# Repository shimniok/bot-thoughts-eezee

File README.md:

A variety of gizmos I created to make breadboard prototyping quick and easy:

* [eeZeeAmp](https://github.com/shimniok/eeZeeAmp) - LM386 circuit, breakout
* [eeZee Tiny](https://github.com/shimniok/eeZeeTiny) - a breadboard target / breakout for 8-pin ATtiny chips
* [eeZee Medium Tiny](https://github.com/shimniok/eeZeeMedTiny) - a breadboard target / breakout for 14-pin ATtiny24/44/84
* [eeZee Tiny841](https://github.com/shimniok/eeZeeTiny841) - breakout for powerful new ATtiny841
* [eeZee Big Tiny](https://github.com/shimniok/eeZeeBigTiny) - a breadboard target / breakout for 20-pin ATtiny2313/4313
* [eeZee Prop](https://github.com/shimniok/eeZeeProp) - breadboard friendly, low cost Propeller board
* [eeZee LED](https://github.com/shimniok/eeZeeLED) - LED + resistor breakout for breadboard
* [eeZee microSD](https://github.com/shimniok/eeZeeMicroSD) - add an SD card to your breadboard Arduino / AVR
* [eeZee Pot](https://github.com/shimniok/eeZeePot)
* [eeZee Power](https://github.com/shimniok/eeZeePower) - small, simple, 5V/3.3V convenient USB breadboard power adapter
* [eeZee PowerJack](https://github.com/shimniok/eeZeePowerJack) - small, simple 5V breadboard power adapter with 2.1mm jack
* [eeZee RGB](https://github.com/shimniok/eeZeeRGB) - WS2812B smart RGB LED breakout
* [eeZee Switch](https://github.com/shimniok/eeZeeSwitch) - breadboard switch with debounce, pull-up
* [eeZee Crystal](https://github.com/shimniok/eeZeeCrystal) - clean up your Arduino / AVR breadboard
* [eeZee VGA](http://github.com/shimniok/eeZeeVGA) - VGA breadboard adapter for Propeller

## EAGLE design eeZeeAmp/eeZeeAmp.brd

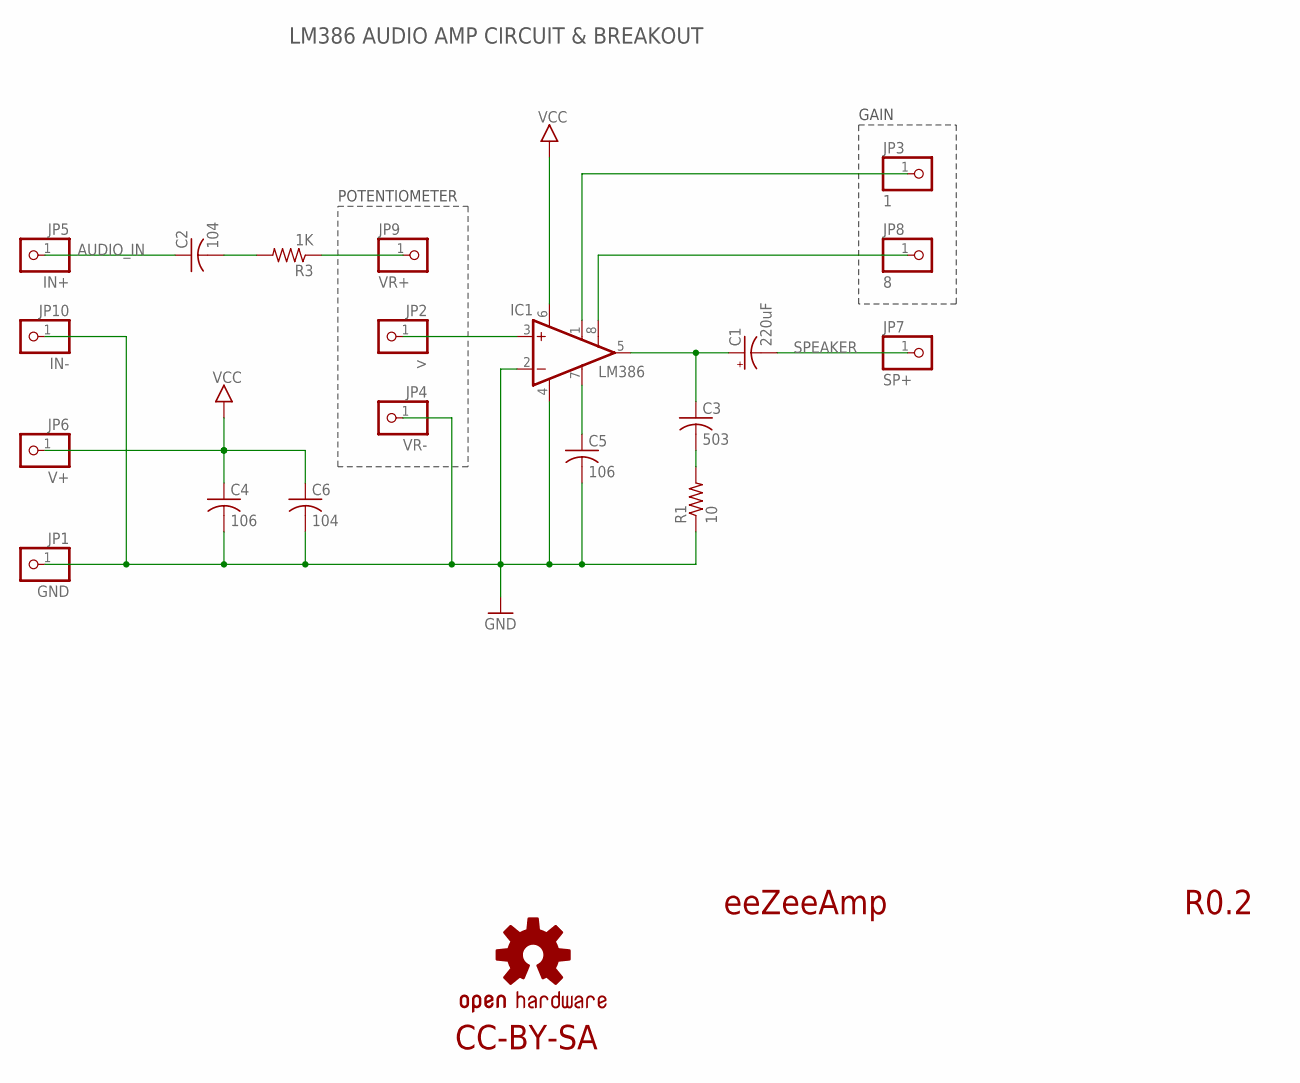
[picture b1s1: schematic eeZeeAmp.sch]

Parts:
C1: 220uF; E3,5-8
C2, C6: 104; C0603
C3: 503; C0603
C4, C5: 106; C1206
IC1: LM386; SO08
JP1: GND; 1X01-S
JP2: >; 1X01-S
JP3: 1; 1X01-S
JP4: VR-; 1X01-S
JP5: IN+; 1X01-S
JP6: V+; 1X01-S
JP7: SP+; 1X01-S
JP8: 8; 1X01-S
JP9: VR+; 1X01-S
JP10: IN-; 1X01-S
LOGO2: OSHW-LOGOS; OSHW-LOGO-S
R1: 10; R0603
R3: 1K; R0603

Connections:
1: IC1.1 (GAIN), JP3.1
3: IC1.3 (+IN), JP2.1
5: C1.+, C3.1, IC1.5 (OUT)
7: C5.1, IC1.7 (BYPASS)
8: IC1.8 (GAIN), JP8.1
AUDIO_IN: C2.1, JP5.1
GND: C4.2, C5.2, C6.2, IC1.2 (-IN), IC1.4 (GND), JP1.1, JP4.1, JP10.1, R1.1
unnamed: C2.2, R3.2
unnamed: C3.2, R1.2
unnamed: JP9.1, R3.1
SPEAKER: C1.-, JP7.1
VCC: C4.1, C6.1, IC1.6 (VS), JP6.1

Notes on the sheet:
eeZeeAmp
R0.2
POTENTIOMETER
LM386 AUDIO AMP CIRCUIT & BREAKOUT
GAIN
CC-BY-SA

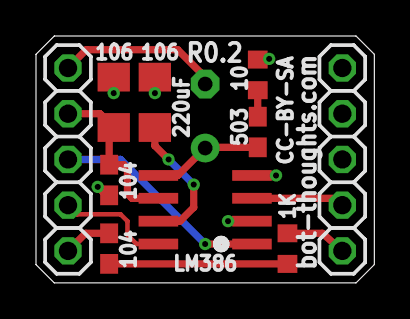
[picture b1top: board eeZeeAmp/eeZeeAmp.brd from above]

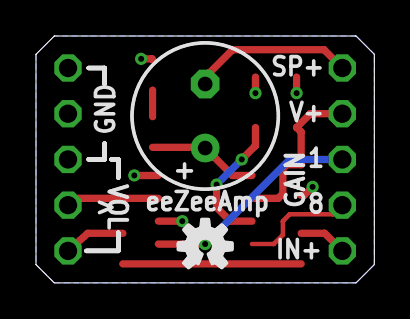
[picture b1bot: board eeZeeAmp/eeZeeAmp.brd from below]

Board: 2 copper layers, 18.8 x 13.7 mm, 20 parts (2 on the bottom side), 12 nets.

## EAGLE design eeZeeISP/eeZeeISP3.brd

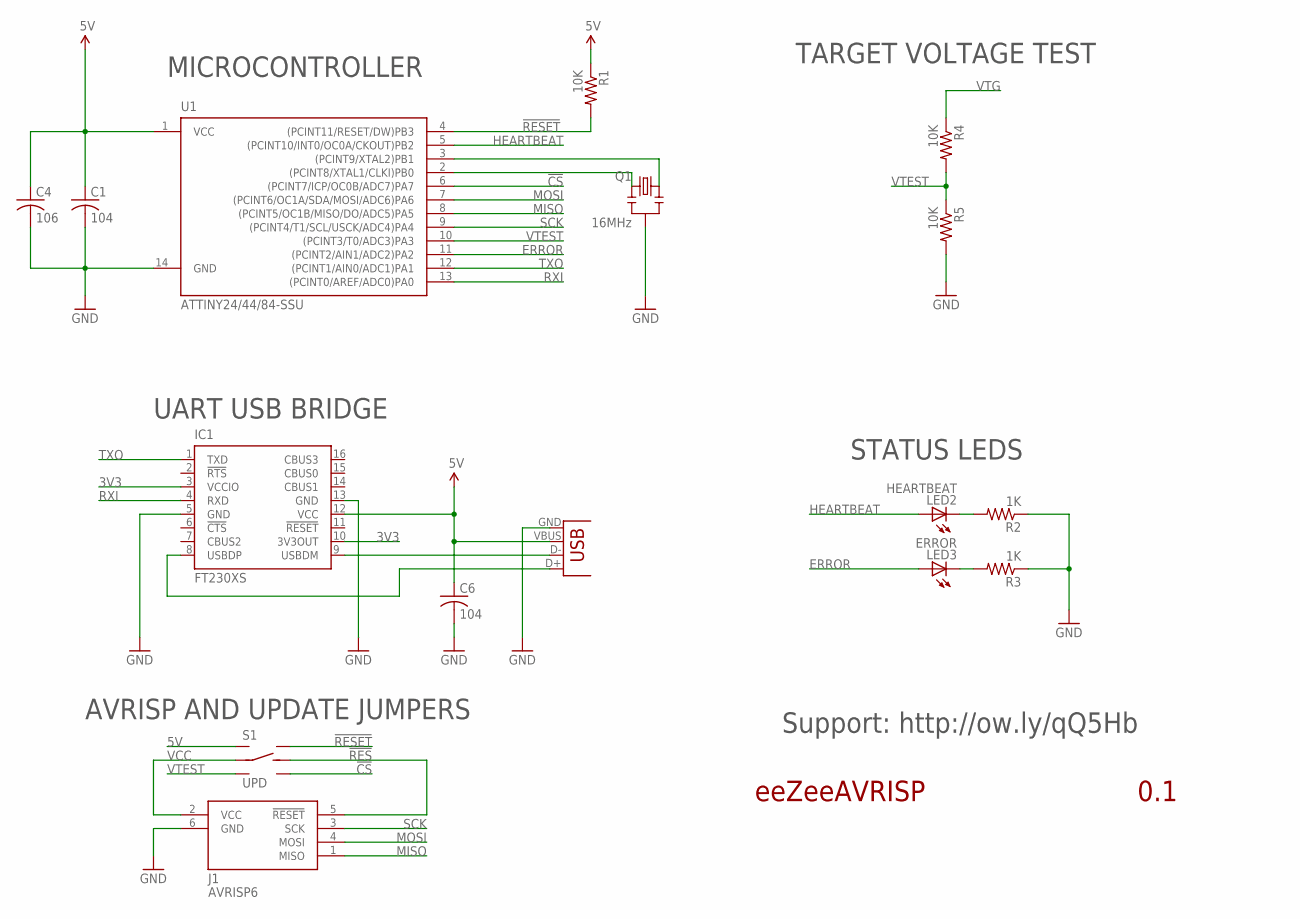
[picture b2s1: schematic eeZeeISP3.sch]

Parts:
C1, C6: 104; C0603
C4: 106; C0603
IC1: FT230XS; SSOP16
J1: AVRISP6; CON6P2R
LED2: HEARTBEAT; CHIPLED_1206
LED3: ERROR; CHIPLED_1206
Q1: 16MHz; CSTCE_V_C
R1, R4, R5: 10K; R0603
R2, R3: 1K; R0603
S1: UPD; DPDT_JS202011CQN
U1: ATTINY24/44/84-SSU; SOIC14
X2: USB-SMD-NS; USB-MINIB-NOSTOP

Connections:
3V3: IC1.3 (VCCIO), IC1.10 (3V3OUT)
5V: C1.1, C4.1, C6.1, IC1.12 (VCC), R1.1, S1.1 (L1), U1.1 (VCC), X2.VBUS
!CS: S1.6 (R2), U1.6 ((PCINT7/ICP/OC0B/ADC7)PA7)
!RES: J1.5 (!RESET), S1.5 (RC)
!RESET: R1.2, S1.4 (R1), U1.4 ((PCINT11/RESET/DW)PB3)
ERROR: LED3.A, U1.11 ((PCINT2/AIN1/ADC2)PA2)
GND: C1.2, C4.2, C6.2, IC1.5 (GND), IC1.13 (GND), J1.6 (GND), Q1.GND, R2.1, R3.1, R5.2, U1.14 (GND), X2.GND
HEARTBEAT: LED2.A, U1.5 ((PCINT10/INT0/OC0A/CKOUT)PB2)
MISO: J1.1 (MISO), U1.8 ((PCINT5/OC1B/MISO/DO/ADC5)PA5)
MOSI: J1.4 (MOSI), U1.7 ((PCINT6/OC1A/SDA/MOSI/ADC6)PA6)
unnamed: Q1.X1, U1.3 ((PCINT9/XTAL2)PB1)
unnamed: IC1.8 (USBDP), X2.D+
unnamed: LED2.C, R2.2
unnamed: LED3.C, R3.2
unnamed: Q1.X2, U1.2 ((PCINT8/XTAL1/CLKI)PB0)
unnamed: IC1.9 (USBDM), X2.D-
RXI: IC1.4 (RXD), U1.13 ((PCINT0/AREF/ADC0)PA0)
SCK: J1.3 (SCK), U1.9 ((PCINT4/T1/SCL/USCK/ADC4)PA4)
TXO: IC1.1 (TXD), U1.12 ((PCINT1/AIN0/ADC1)PA1)
VCC: J1.2 (VCC), S1.2 (LC)
VTEST: R4.2, R5.1, S1.3 (L2), U1.10 ((PCINT3/T0/ADC3)PA3)
VTG: R4.1

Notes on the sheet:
eeZeeAVRISP
0.1
AVRISP AND UPDATE JUMPERS
TARGET VOLTAGE TEST
STATUS LEDS
UART USB BRIDGE
MICROCONTROLLER
Support: http://ow.ly/qQ5Hb

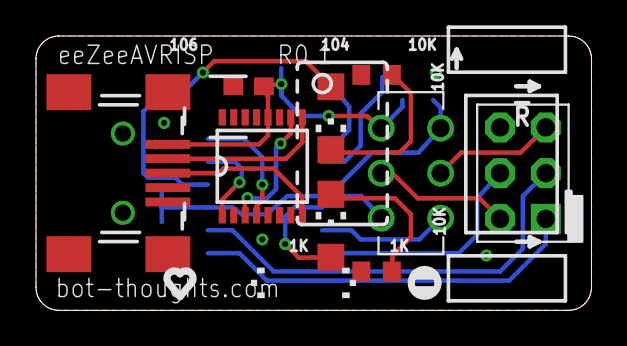
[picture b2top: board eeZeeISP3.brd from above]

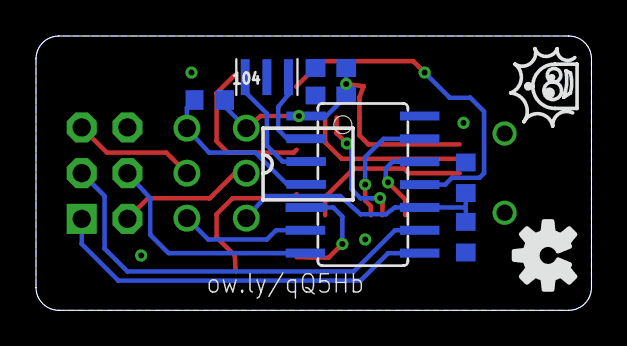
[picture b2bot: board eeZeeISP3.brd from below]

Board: 2 copper layers, 30.9 x 15.2 mm, 16 parts (7 on the bottom side), 21 nets.

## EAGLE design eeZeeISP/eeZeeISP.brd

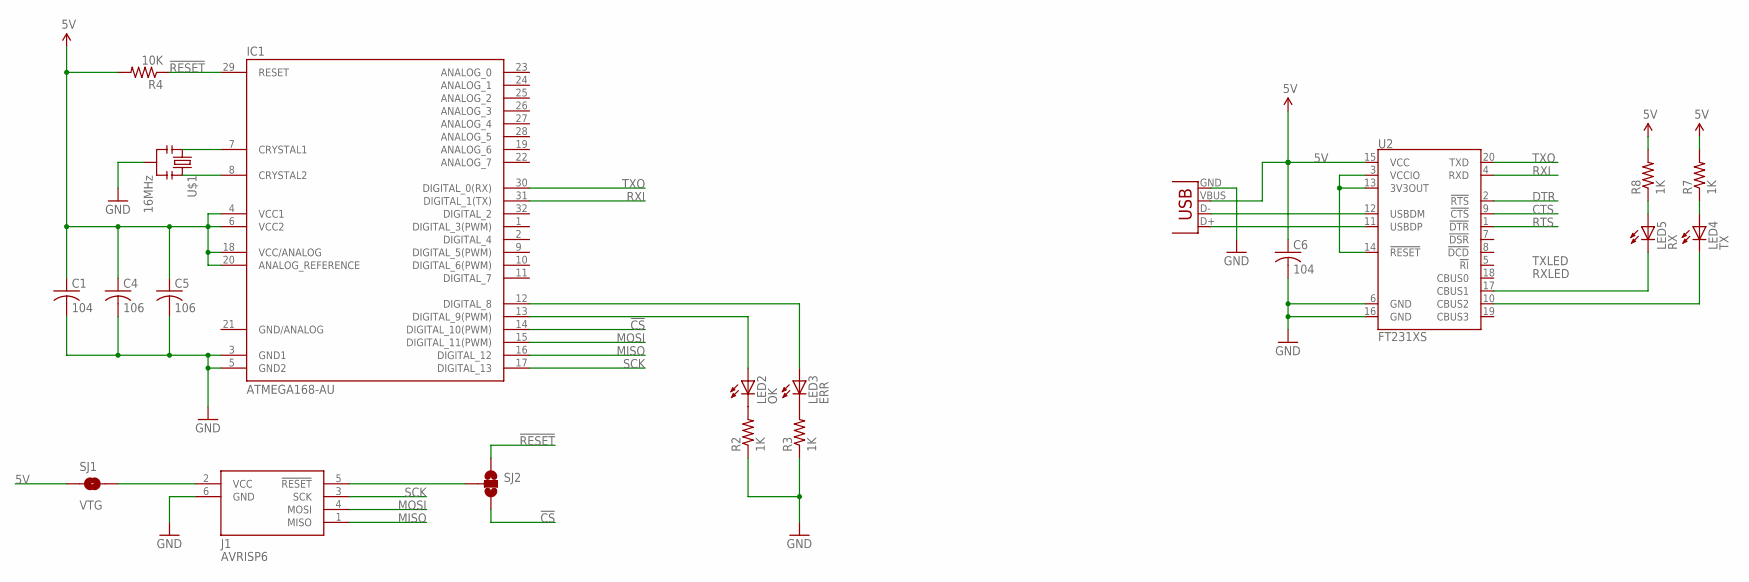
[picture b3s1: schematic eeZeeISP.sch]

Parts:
C1, C6: 104; C0603
C4, C5: 106; C0603
IC1: ATMEGA168-AU; TQFP32-08
J1: AVRISP6; CON6P2R
LED2: OK; CHIPLED_1206
LED3: ERR; CHIPLED_1206
LED4: TX; CHIPLED_1206
LED5: RX; CHIPLED_1206
R2, R3, R7, R8: 1K; R0603
R4: 10K; R0603
SJ1: VTG; SJ_2S-NO
SJ2: SOLDERJUMPER_2WAYS; SJ_3
U2: FT231XS; SSOP20_L
U$1: 16MHz; CSTCE_V_C
X2: USB-SMD-NS; USB-MINIB-NOSTOP

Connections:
5V: C1.1, C4.1, C5.1, C6.1, IC1.4 (VCC1), IC1.6 (VCC2), IC1.18 (VCC/ANALOG), IC1.20 (ANALOG_REFERENCE), R4.2, R7.2, R8.2, SJ1.1, U2.15 (VCC), X2.VBUS
!CS: IC1.14 (DIGITAL_10(PWM)), SJ2.3
!RESET: IC1.29 (RESET), R4.1, SJ2.1
CTS: U2.9 (!CTS)
DTR: U2.1 (!DTR)
GND: C1.2, C4.2, C5.2, C6.2, IC1.3 (GND1), IC1.5 (GND2), J1.6 (GND), R2.1, R3.1, U2.6 (GND), U2.16 (GND), U$1.GND, X2.GND
GND/ANALOG: IC1.21 (GND/ANALOG)
MISO: IC1.16 (DIGITAL_12), J1.1 (MISO)
MOSI: IC1.15 (DIGITAL_11(PWM)), J1.4 (MOSI)
unnamed: LED4.A, R7.1
unnamed: LED5.A, R8.1
unnamed: J1.2 (VCC), SJ1.2
unnamed: J1.5 (!RESET), SJ2.2
unnamed: IC1.13 (DIGITAL_9(PWM)), LED2.A
unnamed: IC1.12 (DIGITAL_8), LED3.A
unnamed: IC1.7 (CRYSTAL1), U$1.X1
unnamed: U2.3 (VCCIO), U2.13 (3V3OUT), U2.14 (!RESET)
unnamed: LED2.C, R2.2
unnamed: LED3.C, R3.2
unnamed: IC1.8 (CRYSTAL2), U$1.X2
RTS: U2.2 (!RTS)
RXI: IC1.31 (DIGITAL_1(TX)), U2.4 (RXD)
RXLED: LED5.C, U2.17 (CBUS1)
SCK: IC1.17 (DIGITAL_13), J1.3 (SCK)
TXLED: LED4.C, U2.10 (CBUS2)
TXO: IC1.30 (DIGITAL_0(RX)), U2.20 (TXD)
USB_D+: U2.11 (USBDP), X2.D+
USB_D-: U2.12 (USBDM), X2.D-

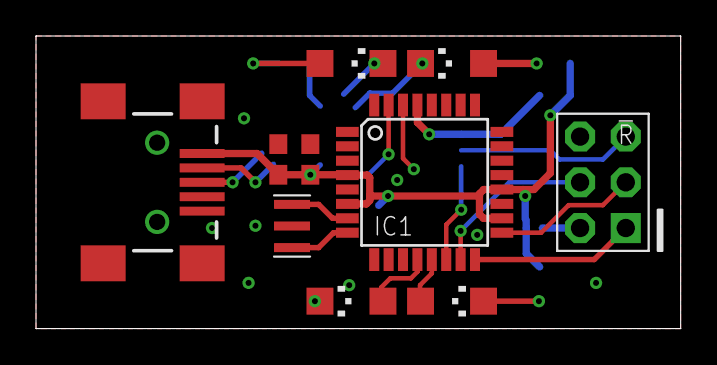
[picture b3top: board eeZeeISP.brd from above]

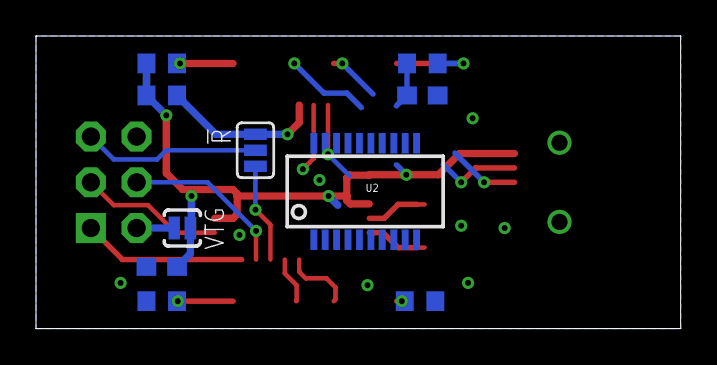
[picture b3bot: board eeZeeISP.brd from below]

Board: 2 copper layers, 35.8 x 16.3 mm, 20 parts (10 on the bottom side), 24 nets.

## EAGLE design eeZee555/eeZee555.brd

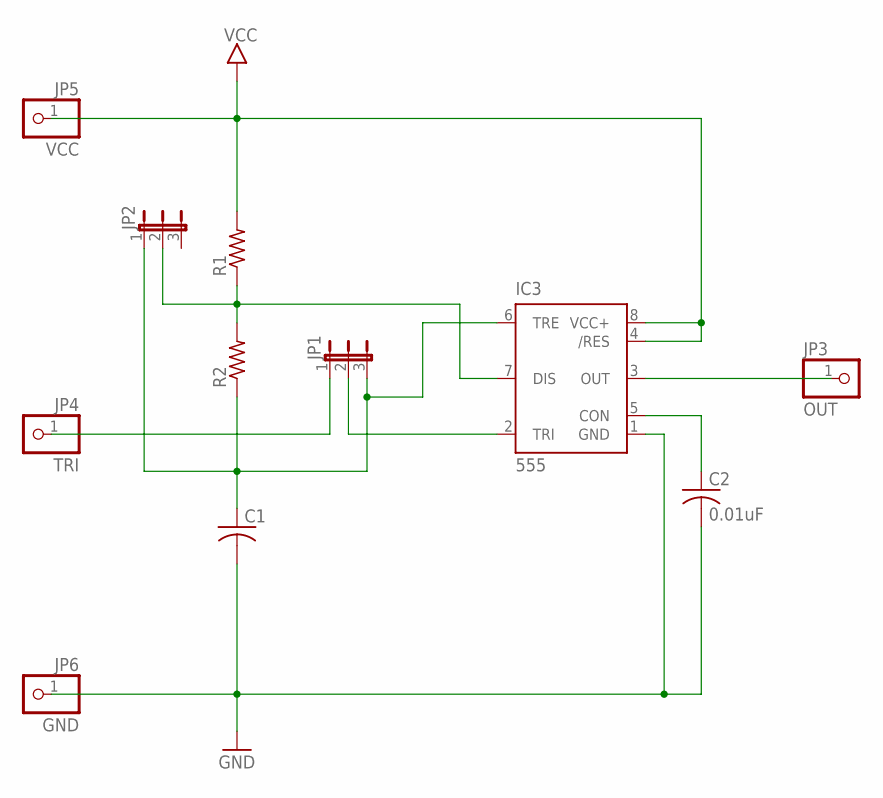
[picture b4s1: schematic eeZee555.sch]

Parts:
C1: C-US050-025X075; C050-025X075
C2: 0.01uF; C0603
IC3: 555; DIL-08
JP1, JP2: JP2E; JP2
JP3: OUT; 1X01-S
JP4: TRI; 1X01-S
JP5: VCC; 1X01-S
JP6: GND; 1X01-S
R1, R2: R-US_0204/5; 0204/5

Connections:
GND: C1.2, C2.2, IC3.1 (GND), JP6.1
unnamed: IC3.7 (DIS), JP2.2, R1.1, R2.2
unnamed: C1.1, IC3.6 (TRE), JP1.3, JP2.1, R2.1
unnamed: JP1.1, JP4.1
unnamed: IC3.2 (TRI), JP1.2
unnamed: IC3.3 (OUT), JP3.1
unnamed: C2.1, IC3.5 (CON)
VCC: IC3.4 (/RES), IC3.8 (VCC+), JP5.1, R1.2

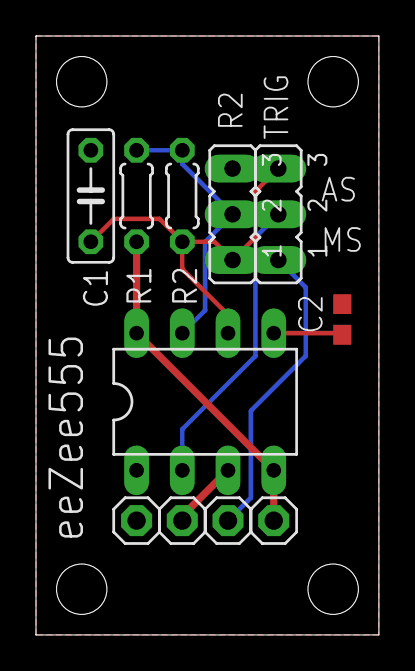
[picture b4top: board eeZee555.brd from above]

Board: 2 copper layers, 19.1 x 33.3 mm, 11 parts (0 on the bottom side), 8 nets.

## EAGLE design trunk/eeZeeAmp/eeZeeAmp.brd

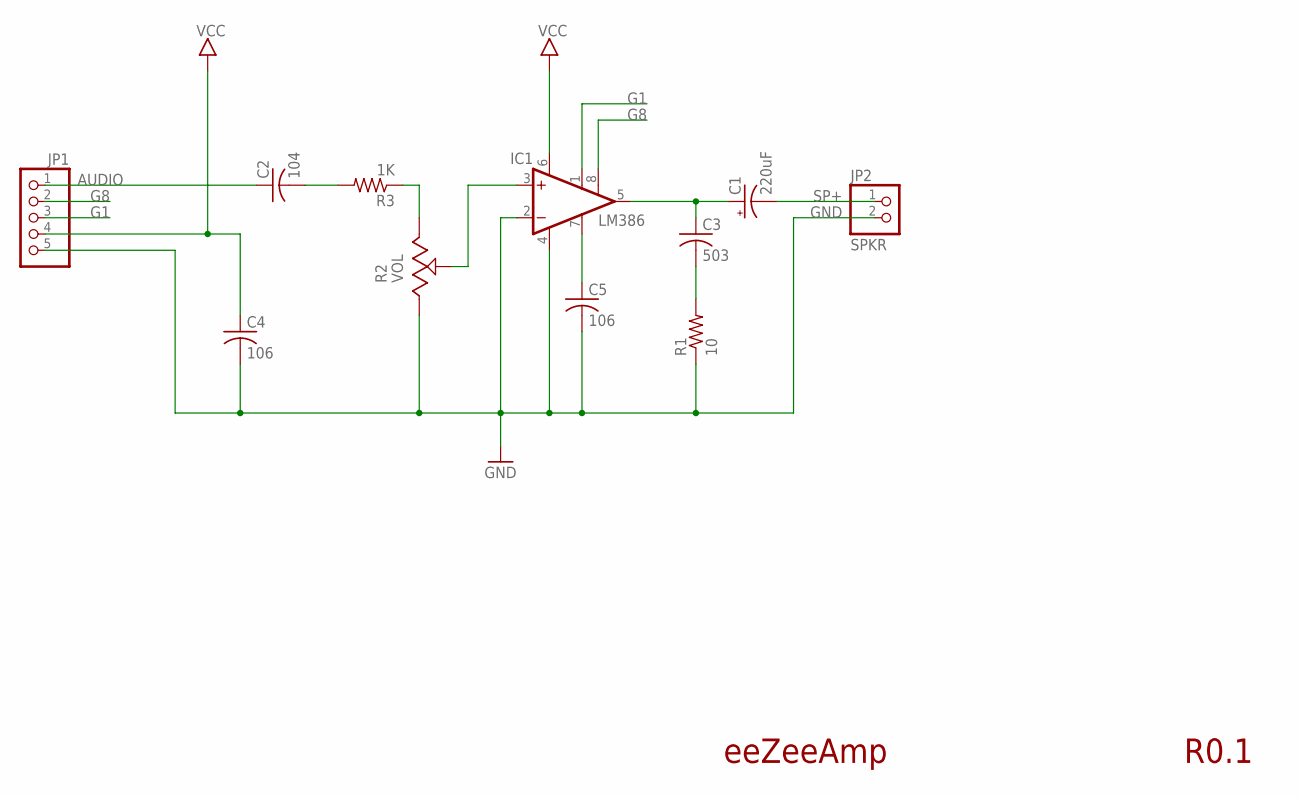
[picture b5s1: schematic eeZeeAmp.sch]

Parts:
C1: 220uF; E2,5-6
C2: 104; C0603
C3: 503; C0603
C4, C5: 106; C1206
IC1: LM386; SO08
JP1: PINHD-1X05_2.54-S; 1X05-S
JP2: SPKR; 1X02-S
R1: 10; R0603
R2: VOL; OFFBOARD_POT_3
R3: 1K; R0603

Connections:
AUDIO: C2.1, JP1.1
G1: IC1.1 (GAIN), JP1.3
G8: IC1.8 (GAIN), JP1.2
GND: C4.2, C5.2, IC1.2 (-IN), IC1.4 (GND), JP1.5, JP2.2, R1.1, R2.P$1 (A)
unnamed: IC1.3 (+IN), R2.P$2 (S)
unnamed: C2.2, R3.2
unnamed: C1.+, C3.1, IC1.5 (OUT)
unnamed: C3.2, R1.2
unnamed: C5.1, IC1.7 (BYPASS)
unnamed: R2.P$3 (E), R3.1
SP+: C1.-, JP2.1
VCC: C4.1, IC1.6 (VS), JP1.4

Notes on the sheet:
eeZeeAmp
R0.1

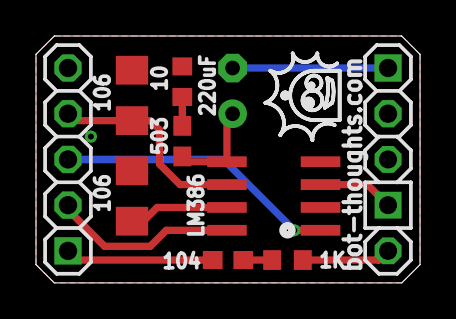
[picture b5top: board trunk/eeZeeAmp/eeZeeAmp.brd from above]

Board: 2 copper layers, 21.3 x 13.7 mm, 11 parts (1 on the bottom side), 12 nets.

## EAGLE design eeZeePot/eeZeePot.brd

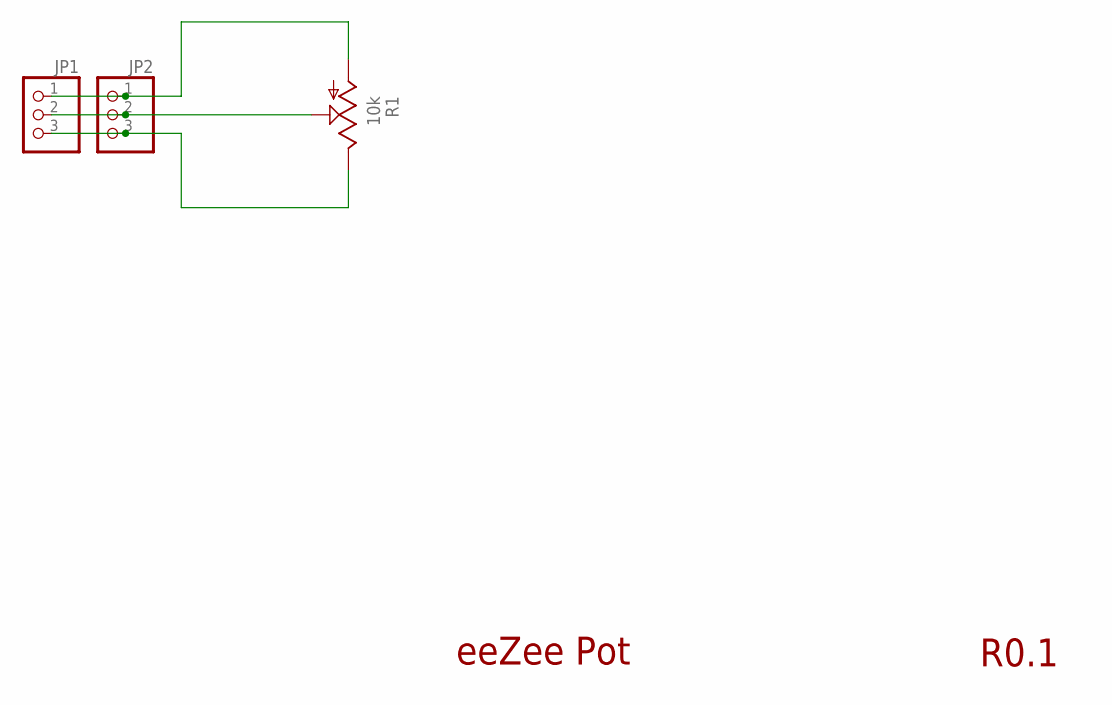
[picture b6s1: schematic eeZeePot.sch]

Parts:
JP1, JP2: PINHD-1X03_2.54-S; 1X03-S
R1: 10k; CA6V

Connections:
unnamed: JP1.1, JP2.1, R1.A
unnamed: JP1.2, JP2.2, R1.S
unnamed: JP1.3, JP2.3, R1.E

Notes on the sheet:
eeZee Pot
R0.1

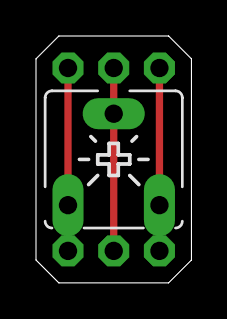
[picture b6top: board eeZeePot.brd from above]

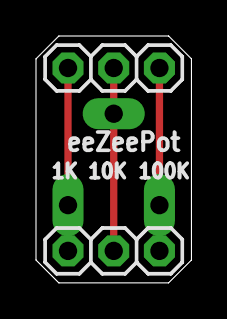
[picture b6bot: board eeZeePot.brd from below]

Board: 2 copper layers, 8.6 x 13.7 mm, 3 parts (2 on the bottom side), 3 nets.

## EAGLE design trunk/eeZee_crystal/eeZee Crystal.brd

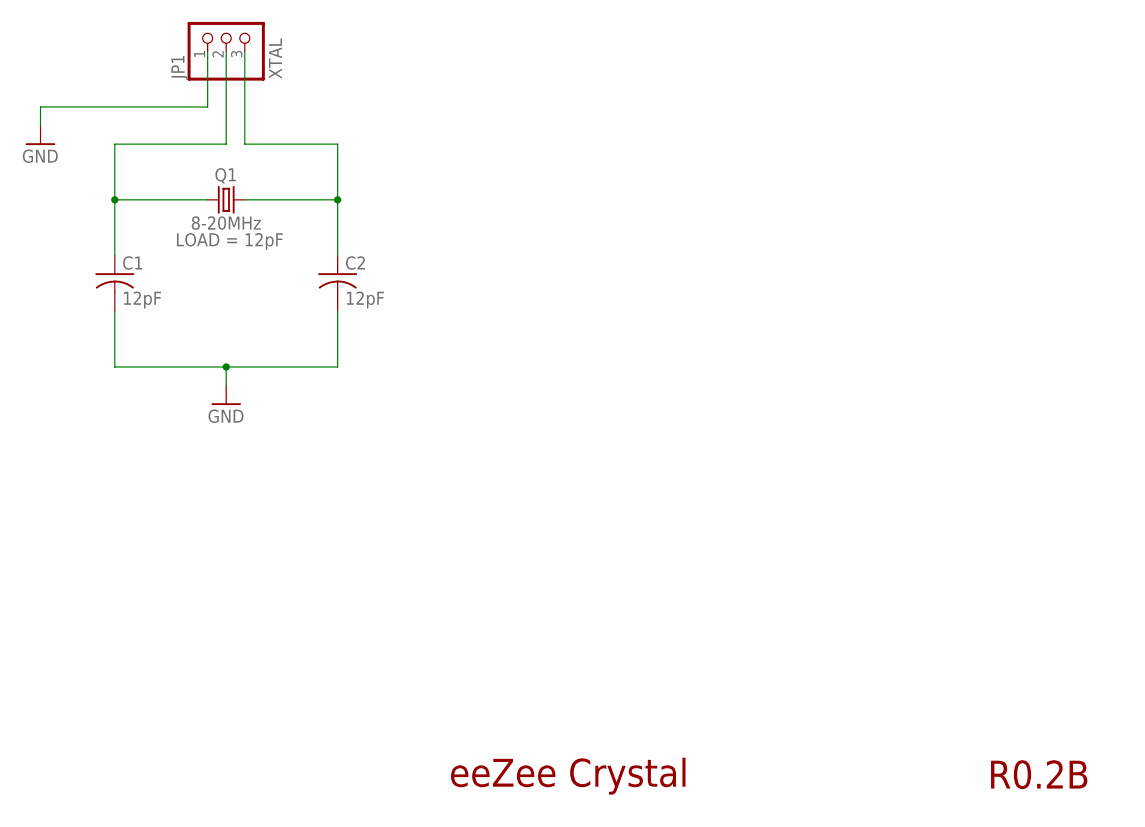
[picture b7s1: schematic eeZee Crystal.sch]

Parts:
C1, C2: 12pF; C0603; PARTNO C1608C0G1H080D
JP1: XTAL; 1X03-S
Q1: 8-20MHz; NDK_2PAD_5X3; PARTNO NX5032GA-16.000000MHZ-LN-CD-1

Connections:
GND: C1.2, C2.2, JP1.1
unnamed: C1.1, JP1.2, Q1.P$2 (2)
unnamed: C2.1, JP1.3, Q1.P$1 (1)

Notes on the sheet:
eeZee Crystal
R0.2B

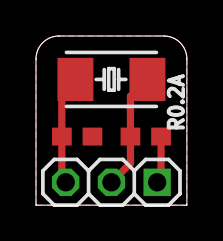
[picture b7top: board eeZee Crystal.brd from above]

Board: 2 copper layers, 8.4 x 9.4 mm, 4 parts (0 on the bottom side), 3 nets.

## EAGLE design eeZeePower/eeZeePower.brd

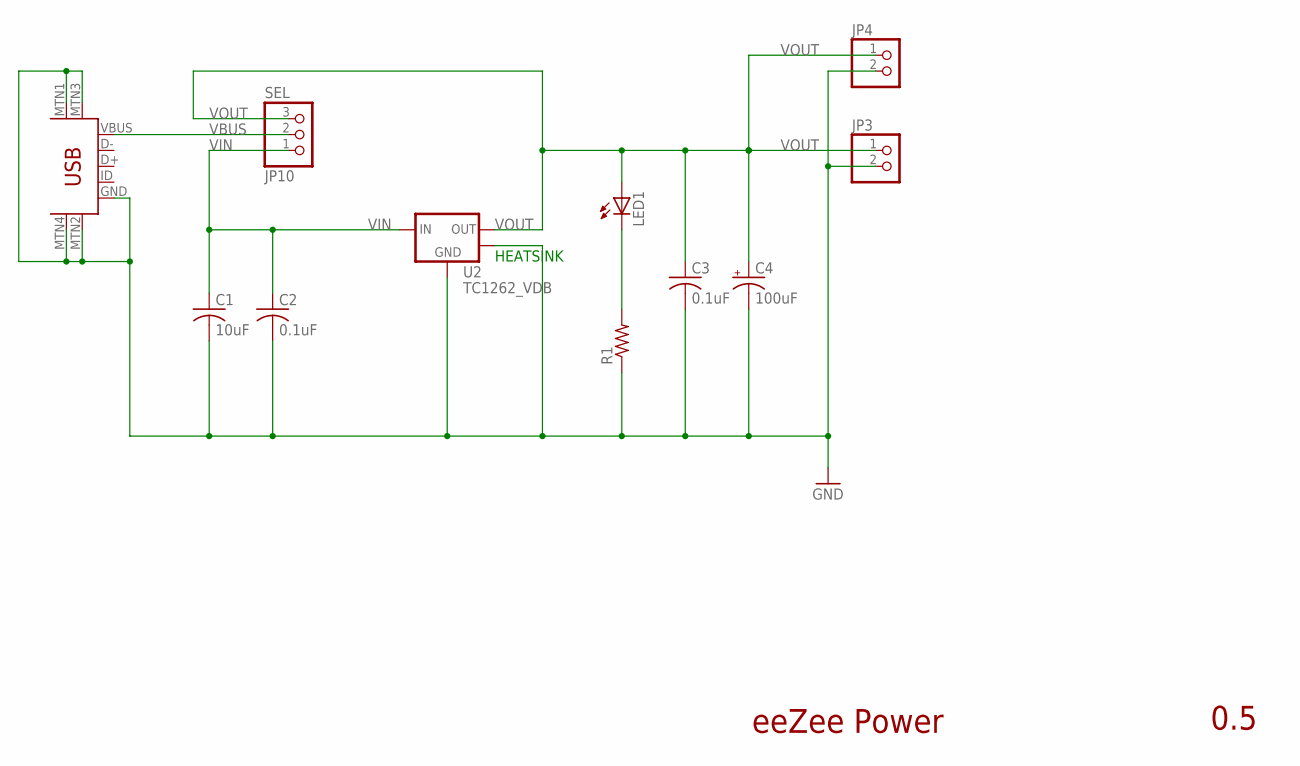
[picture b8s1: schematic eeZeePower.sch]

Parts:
C1: 10uF; C1206
C2, C3: 0.1uF; C0603
C4: 100uF; SMC_B
JP3, JP4: PINHD-1X02_2.54-S; 1X02-S
JP10: SEL; 1X03-S
LED1: LEDCHIPLED_1206; CHIPLED_1206
R1: R-US_R0603; R0603
U2: TC1262_VDB; SOT-223-3
U$1: USB-MINIB-5PIN; USB-MINIB

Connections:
GND: C1.2, C2.2, C3.2, C4.-, JP3.2, JP4.2, R1.1, U2.2 (GND), U2.4 (TAB), U$1.GND, U$1.MTN1 (MTN2), U$1.MTN2 (MTN3), U$1.MTN3 (MTN1), U$1.MTN4
unnamed: LED1.C, R1.2
VBUS: JP10.2, U$1.VBUS
VIN: C1.1, C2.1, JP10.1, U2.1 (VIN)
VOUT: C3.1, C4.+, JP3.1, JP4.1, JP10.3, LED1.A, U2.3 (VOUT)

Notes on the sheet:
eeZee Power
0.5
HEATSINK

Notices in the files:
parts and their libraries:
SparkFun: Licensing: CC v3.0 Share-Alike You are welcome to use this library for commercial purposes.
SparkFun-Aesthetics: Licensing: Creative Commons ShareAlike 4.0 International - https://creativecommons.org/licenses/by-sa/4.0
